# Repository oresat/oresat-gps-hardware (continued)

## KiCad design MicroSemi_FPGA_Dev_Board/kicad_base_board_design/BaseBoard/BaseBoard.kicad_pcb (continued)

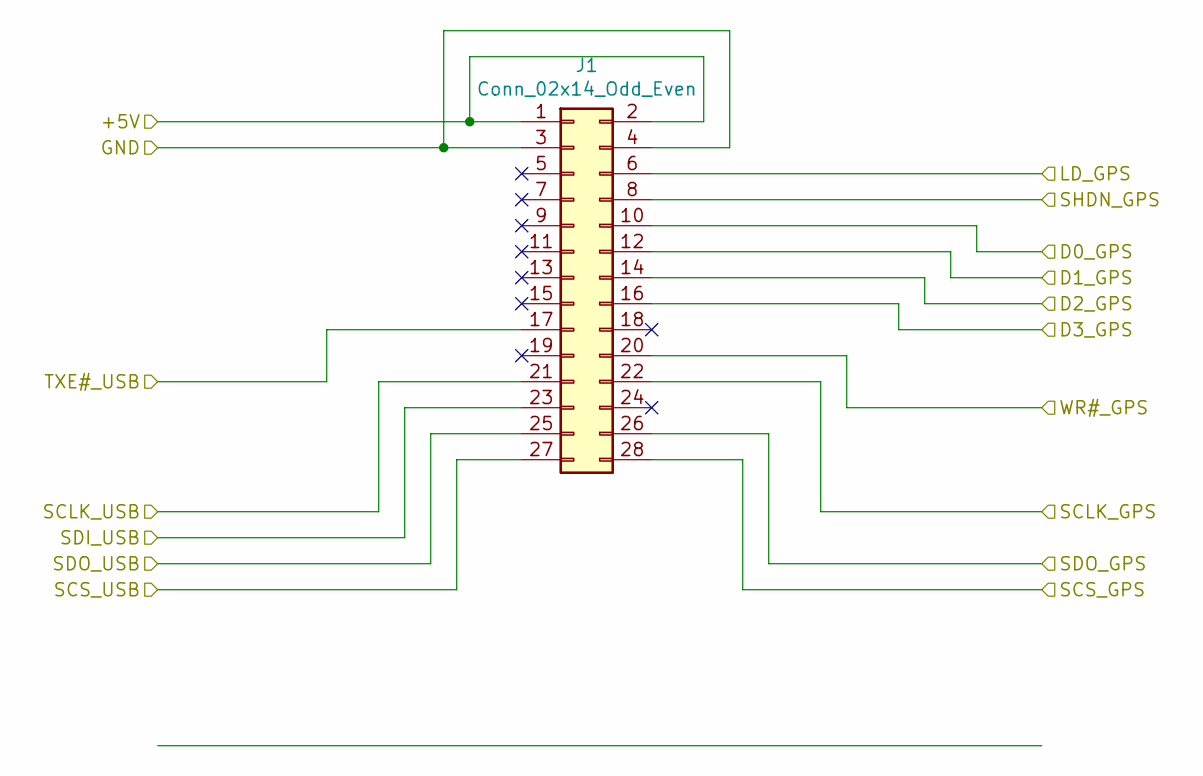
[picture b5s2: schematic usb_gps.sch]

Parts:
J1: Conn_02x14_Odd_Even; PinHeader_2x14_P2.54mm_Vertical

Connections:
/Sheet5DD758E7/+5V: J1.1, J1.2; also elsewhere on the board
/Sheet5DD758E7/D0_GPS: J1.10; also elsewhere on the board
/Sheet5DD758E7/D1_GPS: J1.12; also elsewhere on the board
/Sheet5DD758E7/D2_GPS: J1.14; also elsewhere on the board
/Sheet5DD758E7/D3_GPS: J1.16; also elsewhere on the board
/Sheet5DD758E7/LD_GPS: J1.6; also elsewhere on the board
/Sheet5DD758E7/SCLK_GPS: J1.22; also elsewhere on the board
/Sheet5DD758E7/SCLK_USB: J1.21; also elsewhere on the board
/Sheet5DD758E7/SCS_GPS: J1.28; also elsewhere on the board
/Sheet5DD758E7/SCS_USB: J1.27; also elsewhere on the board
/Sheet5DD758E7/SDI_USB: J1.23; also elsewhere on the board
/Sheet5DD758E7/SDO_GPS: J1.26; also elsewhere on the board
/Sheet5DD758E7/SDO_USB: J1.25; also elsewhere on the board
/Sheet5DD758E7/SHDN_GPS: J1.8; also elsewhere on the board
/Sheet5DD758E7/TXE#_USB: J1.17; also elsewhere on the board
/Sheet5DD758E7/WR#_GPS: J1.20; also elsewhere on the board
GND: J1.3, J1.4; also elsewhere on the board

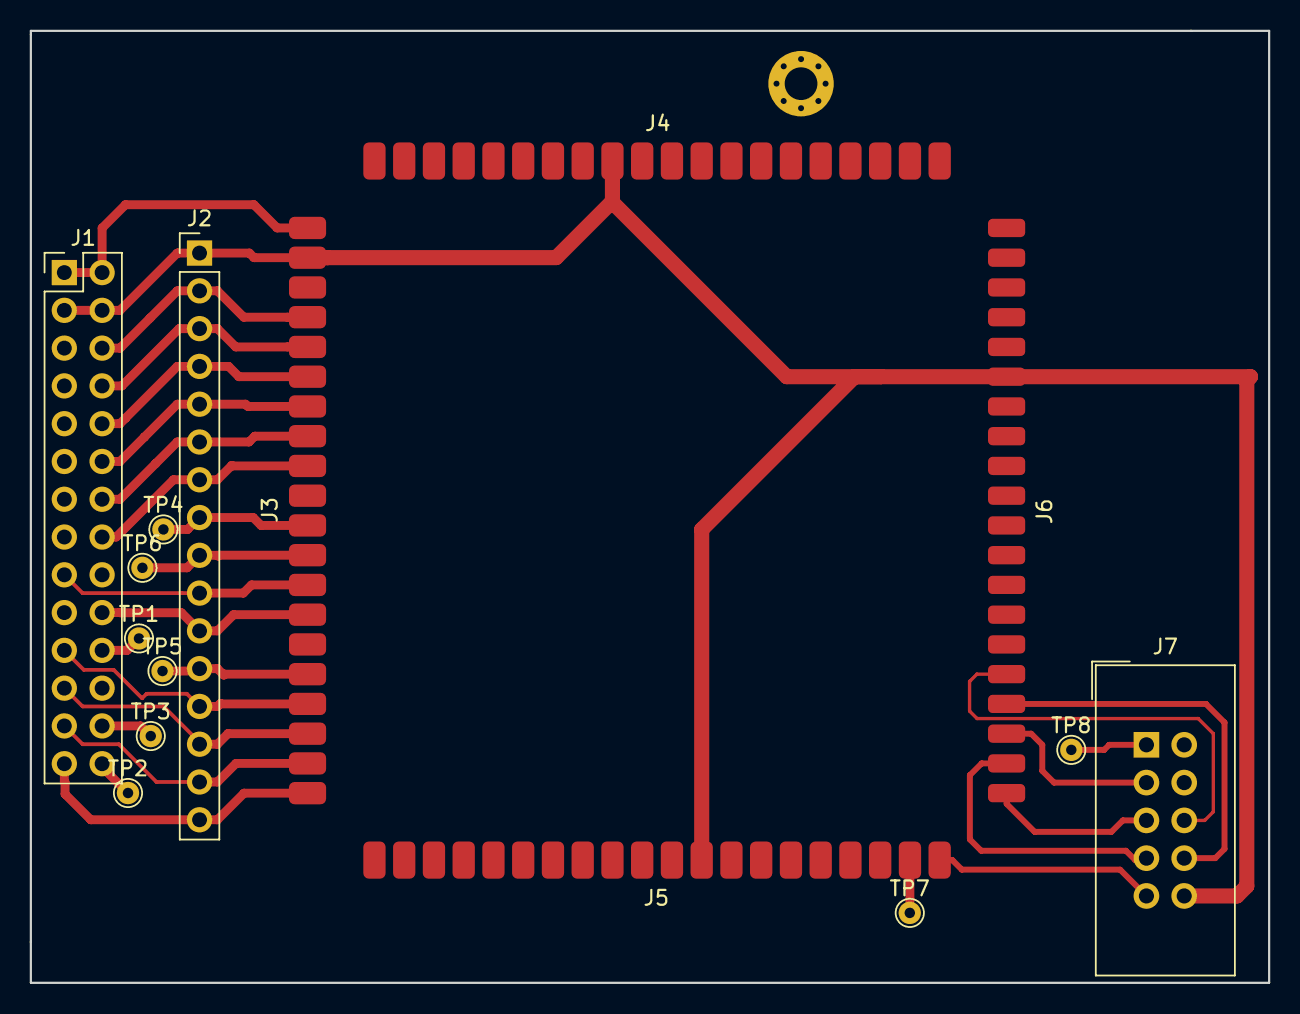
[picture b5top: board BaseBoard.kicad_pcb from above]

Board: 2 copper layers, 83.2 x 64.0 mm, 15 parts (0 on the bottom side), 28 nets.

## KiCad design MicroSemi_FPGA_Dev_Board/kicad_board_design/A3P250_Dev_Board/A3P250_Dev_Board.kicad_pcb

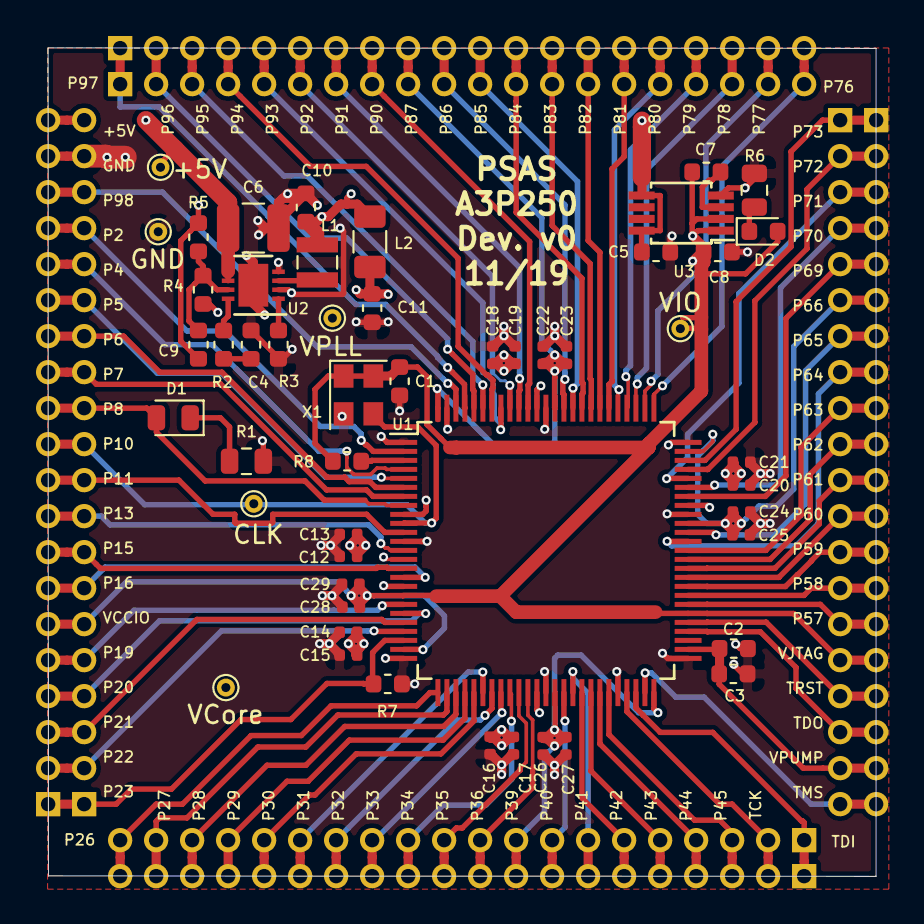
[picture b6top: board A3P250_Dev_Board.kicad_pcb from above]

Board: 4 copper layers, 46.0 x 46.0 mm, 59 parts (0 on the bottom side), 90 nets.

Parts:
+5V: +5V; TestPoint_THTPad_D1.0mm_Drill0.5mm
C1, C3, C7: 0.01uF; C_0603_1608Metric
C2: 0.33uF; C_0603_1608Metric
C4: 680pF; C_0603_1608Metric
C5: 1uF; C_0603_1608Metric
C6: 22uF; C_1210_3225Metric
C8, C10, C11: 10uF; C_0603_1608Metric
C9: 22pF; C_0603_1608Metric
C12, C14, C16, C18, C20, C22, C24, C26, C28: .1uF; C_0402_1005Metric
C13, C15, C17, C19, C21, C23, C25, C27, C29: 0.01uF; C_0402_1005Metric
CLK: VCCIO; TestPoint_THTPad_D1.0mm_Drill0.5mm
D1: LED_ALT; LED_0805_2012Metric
D2: LED_ALT; LED_0603_1608Metric
GND: GND; TestPoint_THTPad_D1.0mm_Drill0.5mm
J1, J1#2, J2, J2#2, J3, J3#2, J4, J4#2: Conn_01x20; PinHeader_1x20_P2.00mm_Vertical
L1: 2.2uH; L_Wuerth_MAPI-2512
L2: 6.8uH; L_1206_3216Metric
R1, R6: 200; R_0805_2012Metric
R2: 16.9K; R_0603_1608Metric
R3: 549K; R_0603_1608Metric
R4: 287K; R_0603_1608Metric
R5: 249K; R_0603_1608Metric
R7, R8: 20K; R_0603_1608Metric
U1: A3P250; LQFP-100_14x14mm_P0.5mm
U2: LTC3561A; DFN-8-1EP_3x3mm_P0.5mm_EP1.66x2.38mm
U3: LT1962-3.3; MSOP-8_3x3mm_P0.65mm
VCore: 1.5V Core; TestPoint_THTPad_D1.0mm_Drill0.5mm
VIO: VCCIO; TestPoint_THTPad_D1.0mm_Drill0.5mm
VPLL: 1.5V PLL; TestPoint_THTPad_D1.0mm_Drill0.5mm
X1: ASE-25MHz; Oscillator_SMD_Abracon_ASE-4Pin_3.2x2.5mm

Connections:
+5V: +5V.1, C5.1, C6.1, J4.20, J4#2.20, U2.5, U2.6, U3.5, U3.8
GAA_IO00RSB0: J4.18, J4#2.18, U1.98
GND: C1.2, C2.2, C3.2, C4.2, C5.2, C6.2, C8.2, C10.2, C11.2, C12.2, C13.2, C14.2, C15.2, C16.2, C17.2, C18.2, C19.2, C20.2, C21.2, C22.2, C23.2, C24.2, C25.2, C26.2, C27.2, C28.2, C29.2, GND.1, J4.19, J4#2.19, R1.2, R3.1, R4.1, R6.2, R7.2, U1.1, U1.9, U1.12, U1.25, U1.38, U1.46, U1.51, U1.67, U1.75, U1.88, U1.99, U2.2, U2.4, U2.9, U3.4, X1.2
unnamed: C4.1, R2.1
unnamed: C7.2, U3.3
unnamed: C9.2, R4.2, R5.2, U2.7
unnamed: C9.1, C10.1, C14.1, C15.1, C16.1, C17.1, C18.1, C19.1, C20.1, C21.1, L1.2, L2.1, R5.1, U1.17, U1.37, U1.68, U1.89, VCore.1
unnamed: C11.1, C12.1, C13.1, L2.2, U1.14, VPLL.1
unnamed: C22.1, C23.1, J1.9, J1#2.9, U1.87, U1.100
unnamed: C24.1, C25.1, J2.6, J2#2.6, U1.66, U1.74
unnamed: C26.1, C27.1, J3.9, J3#2.9, U1.39, U1.50
unnamed: D1.1, R1.1
unnamed: D1.2, J4.12, J4#2.12, U1.8
unnamed: D2.1, R6.1
unnamed: J1.1, J1#2.1, U1.97
unnamed: J1.2, J1#2.2, U1.96
unnamed: J1.3, J1#2.3, U1.95
unnamed: J1.4, J1#2.4, U1.94
unnamed: J1.5, J1#2.5, U1.93
unnamed: J1.6, J1#2.6, U1.92
unnamed: J1.7, J1#2.7, U1.91
unnamed: J1.8, J1#2.8, U1.90
unnamed: J1.10, J1#2.10, U1.86
unnamed: J1.11, J1#2.11, U1.85
unnamed: J1.12, J1#2.12, U1.84
unnamed: J1.13, J1#2.13, U1.83
unnamed: J1.14, J1#2.14, U1.82
unnamed: J1.15, J1#2.15, U1.81
unnamed: J1.16, J1#2.16, U1.80
unnamed: J1.17, J1#2.17, U1.79
unnamed: J1.18, J1#2.18, U1.78
unnamed: J1.19, J1#2.19, U1.77
unnamed: J1.20, J1#2.20, U1.76
unnamed: J2.1, J2#2.1, U1.73
unnamed: J2.2, J2#2.2, U1.72
unnamed: J2.3, J2#2.3, U1.71
unnamed: J2.4, J2#2.4, U1.70
unnamed: J2.5, J2#2.5, U1.69
unnamed: J2.7, J2#2.7, U1.65
unnamed: J2.8, J2#2.8, U1.64
unnamed: J2.9, J2#2.9, U1.63
unnamed: J2.10, J2#2.10, U1.62
unnamed: J2.11, J2#2.11, U1.61
unnamed: J2.12, J2#2.12, U1.60
unnamed: J2.13, J2#2.13, U1.59
unnamed: J2.14, J2#2.14, U1.58
unnamed: J2.15, J2#2.15, U1.57
unnamed: J3.3, J3#2.3, U1.45
unnamed: J3.4, J3#2.4, U1.44
unnamed: J3.5, J3#2.5, U1.43
unnamed: J3.6, J3#2.6, U1.42
unnamed: J3.7, J3#2.7, U1.41
unnamed: J3.8, J3#2.8, U1.40
unnamed: J3.10, J3#2.10, U1.36
unnamed: J3.11, J3#2.11, U1.35
unnamed: J3.12, J3#2.12, U1.34
unnamed: J3.13, J3#2.13, U1.33
unnamed: J3.14, J3#2.14, U1.32
unnamed: J3.15, J3#2.15, U1.31
unnamed: J3.16, J3#2.16, U1.30
unnamed: J3.17, J3#2.17, U1.29
unnamed: J3.18, J3#2.18, U1.28
unnamed: J3.19, J3#2.19, U1.27
unnamed: J3.20, J3#2.20, U1.26
unnamed: J4.1, J4#2.1, R7.1, U1.23
unnamed: J4.2, J4#2.2, U1.22
unnamed: J4.3, J4#2.3, U1.21
unnamed: J4.4, J4#2.4, U1.20
unnamed: J4.5, J4#2.5, U1.19
unnamed: J4.7, J4#2.7, U1.16
unnamed: J4.8, J4#2.8, U1.15
unnamed: J4.9, J4#2.9, U1.13
unnamed: J4.10, J4#2.10, U1.11
unnamed: CLK.1, J4.11, J4#2.11, U1.10, X1.3
unnamed: J4.13, J4#2.13, U1.7
unnamed: J4.14, J4#2.14, U1.6
unnamed: J4.15, J4#2.15, U1.5
unnamed: J4.16, J4#2.16, U1.4
unnamed: J4.17, J4#2.17, U1.2
unnamed: L1.1, U2.3
unnamed: R2.2, U2.8
unnamed: R3.2, U2.1
unnamed: R8.2, U1.3
TCK: J3.2, J3#2.2, U1.47
TDI: J3.1, J3#2.1, U1.48
TDO: J2.18, J2#2.18, U1.54
TMS: J2.20, J2#2.20, U1.49
TRST: J2.17, J2#2.17, U1.55
VCCIB3: C1.1, C7.1, C8.1, C28.1, C29.1, D2.2, J2.16, J2#2.16, J4.6, J4#2.6, R8.1, U1.18, U1.24, U1.56, U3.1, U3.2, VIO.1, X1.1, X1.4
VPUMP: C2.1, C3.1, J2.19, J2#2.19, U1.52

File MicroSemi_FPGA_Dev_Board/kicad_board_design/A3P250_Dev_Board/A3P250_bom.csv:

Refs,Value,Footprint,Quantity,MFR,MPN,SPR,SPN
C12;C14;C16;C20;C18,.1uF,Capacitor_SMD:C_0402_1005Metric,5,-,CGA2B1X7R1C104K050BC,Digikey,445-5613-1-ND
C13;C17;C21;C19;C15;C3;C7;C1,0.01uF,Capacitor_SMD:C_0603_1608Metric,8,Kemet,C0603C103K5RAC7081,Digikey,399-C0603C103K5RAC7081CT-ND
C2,0.33uF,Capacitor_SMD:C_0603_1608Metric,1,Yageo,CC0603KRX5R7BB334,Digikey,311-4045-1-ND
C10;C8;C11,10uF,Capacitor_SMD:C_0603_1608Metric,3,Taiyo Yuden,JMK107BJ106MA-T,Digikey,587-1256-1-ND
C5,1uF,Capacitor_SMD:C_0603_1608Metric,1,Samsung,CL10B105KP8NNNC,Digikey,1276-1946-1-ND
C9,22pF,Capacitor_SMD:C_0603_1608Metric,1,Yageo,CC0603JRNPO9BN220,Digikey,311-1062-1-ND
C4,680pF,Capacitor_SMD:C_0603_1608Metric,1,Yageo,CC0603KRX7R9BB681,Digikey,311-1188-1-ND
C6,22uF,Capacitor_SMD:C_1210_3225Metric,1,Taiyo Yuden,JMK325BJ226MM-T,Digikey,587-1384-1-ND
J1;J4;J2;J3,Conn_01x20,Connector_PinHeader_2.00mm:PinHeader_1x20_P2.00mm_Vertical,4,-,-,-,-
L2,6.8uH,Inductor_SMD:L_1206_3216Metric,1,Taiyo Yuden,CB2518T6R8M,Digikey,587-2188-1-ND
L1,2.2uH,Inductor_SMD:L_Wuerth_MAPI-2512,1,Wurth,74405024022,Digikey,732-10776-1-ND
D2,LED_ALT,LED_SMD:LED_0603_1608Metric,1,Lite-On,LTST-C191KGKT,Digikey,160-1446-2-ND
D1,LED_ALT,LED_SMD:LED_0805_2012Metric,1,Lite-On,LTST-C171KRKT,Digikey,160-1427-1-ND
X1,ASE-25MHz,Oscillator:Oscillator_SMD_Abracon_ASE-4Pin_3.2x2.5mm,1,Abracon,ASE-25.000MHZ-LC-T,Digikey,535-9568-1-ND
U2,LTC3561A,Package_DFN_QFN:DFN-8-1EP_3x3mm_P0.5mm_EP1.66x2.38mm,1,Analog Devices,LTC3561AEDD#TRPBFCT-ND,Digikey,LTC3561AEDD#TRPBFCT-ND
U1,A3P250,Package_QFP:LQFP-100_14x14mm_P0.5mm,1,Microsemi,A3P250-VQG100,Digikey,1100-1030-ND
U3,LT1962-3.3,Package_SO:MSOP-8_3x3mm_P0.65mm,1,Analog Devices,LT1962EMS8-3.3#PBF,Digikey,LT1962EMS8-3.3#PBF-ND
R2,16.9K,Resistor_SMD:R_0603_1608Metric,1,Yageo,RT0603DRE0716K9L,Digikey,311-2441-1-ND
R5,249K,Resistor_SMD:R_0603_1608Metric,1,Yageo,RT0603BRD07249KL,Digikey,YAG4510CT-ND
R4,287K,Resistor_SMD:R_0603_1608Metric,1,Yageo,RT0603BRD07287KL,Digikey,YAG1609CT-ND
R3,549K,Resistor_SMD:R_0603_1608Metric,1,Yageo,RC0603FR-07549KL,Digikey,311-549KHRCT-ND
R6;R1,200,Resistor_SMD:R_0805_2012Metric,2,Susumu,RR1220P-201-D,Digikey,RR12P200DCT-ND

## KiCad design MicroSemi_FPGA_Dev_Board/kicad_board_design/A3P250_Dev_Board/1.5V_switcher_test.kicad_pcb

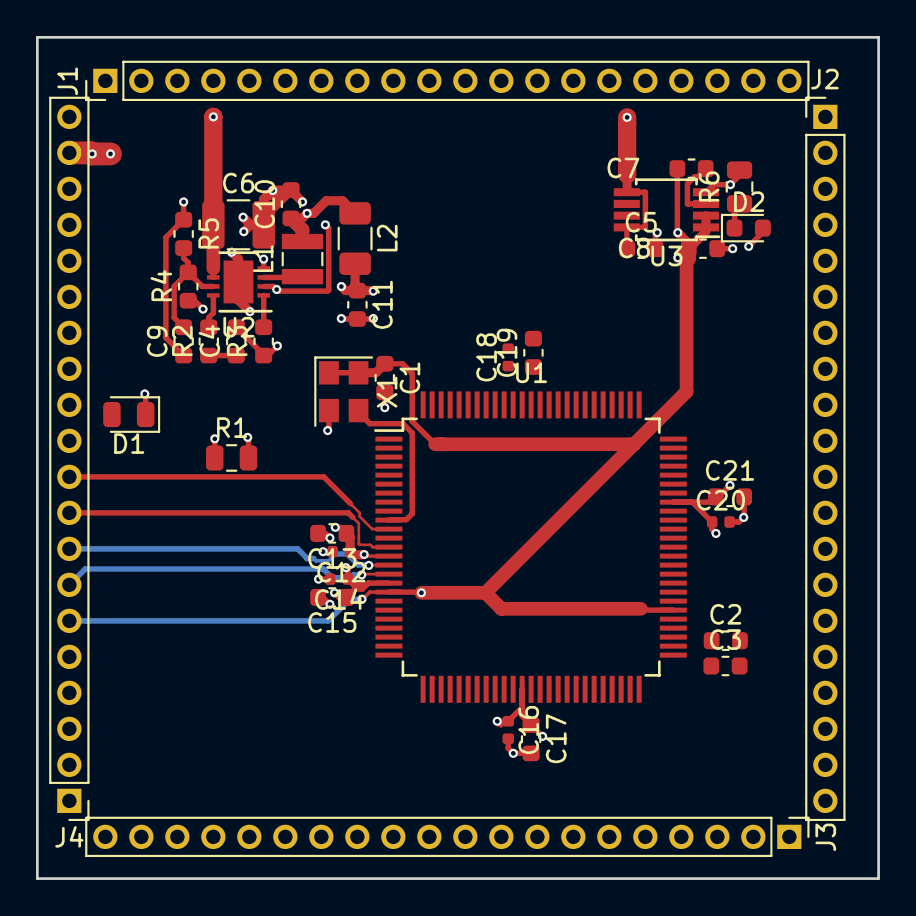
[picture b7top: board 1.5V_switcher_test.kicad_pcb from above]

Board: 4 copper layers, 46.7 x 46.7 mm, 39 parts (0 on the bottom side), 89 nets.

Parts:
C1, C3, C7, C13, C15, C17, C19, C21: 0.01uF; C_0603_1608Metric
C2: 0.33uF; C_0603_1608Metric
C4: 680pF; C_0603_1608Metric
C5: 1uF; C_0603_1608Metric
C6: 22uF; C_1210_3225Metric
C8, C10, C11: 10uF; C_0603_1608Metric
C9: 22pF; C_0603_1608Metric
C12, C14, C16, C18, C20: .1uF; C_0402_1005Metric
D1: LED_ALT; LED_0805_2012Metric
D2: LED_ALT; LED_0603_1608Metric
J1, J2, J3, J4: Conn_01x20; PinHeader_1x20_P2.00mm_Vertical
L1: 2.2uH; L_Wuerth_MAPI-2512
L2: 6.8uH; L_1206_3216Metric
R1, R6: 200; R_0805_2012Metric
R2: 16.9K; R_0603_1608Metric
R3: 549K; R_0603_1608Metric
R4: 287K; R_0603_1608Metric
R5: 249K; R_0603_1608Metric
U1: A3P250; LQFP-100_14x14mm_P0.5mm
U2: LTC3561A; DFN-8-1EP_3x3mm_P0.5mm_EP1.66x2.38mm
U3: LT1962-3.3; MSOP-8_3x3mm_P0.65mm
X1: ASE-25MHz; Oscillator_SMD_Abracon_ASE-4Pin_3.2x2.5mm

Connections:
+5V: C5.1, C6.1, J4.20, U2.5, U2.6, U3.5, U3.8
GAA_IO00RSB0: J4.17, U1.98
GND: C1.2, C2.2, C3.2, C4.2, C5.2, C6.2, C8.2, C10.2, C11.2, C12.2, C13.2, C14.2, C15.2, C16.2, C17.2, C18.2, C19.2, C20.2, C21.2, J4.19, R1.2, R3.1, R4.1, R6.2, U1.1, U1.9, U1.12, U1.24, U1.25, U1.38, U1.46, U1.50, U1.51, U1.67, U1.74, U1.75, U1.88, U1.99, U1.100, U2.2, U2.4, U2.9, U3.4, X1.2
unnamed: C4.1, R2.1
unnamed: C7.2, U3.3
unnamed: C9.2, R4.2, R5.2, U2.7
unnamed: C9.1, C10.1, C14.1, C15.1, C16.1, C17.1, C18.1, C19.1, C20.1, C21.1, L1.2, L2.1, R5.1, U1.17, U1.37, U1.68, U1.89
unnamed: C11.1, C12.1, C13.1, L2.2, U1.14
unnamed: D1.1, R1.1
unnamed: D1.2, J4.12, U1.8
unnamed: D2.1, R6.1
unnamed: J1.1, U1.97
unnamed: J1.2, U1.96
unnamed: J1.3, U1.95
unnamed: J1.4, U1.94
unnamed: J1.5, U1.93
unnamed: J1.6, U1.92
unnamed: J1.7, U1.91
unnamed: J1.8, U1.90
unnamed: J1.9, U1.87
unnamed: J1.10, U1.86
unnamed: J1.11, U1.85
unnamed: J1.12, U1.84
unnamed: J1.13, U1.83
unnamed: J1.14, U1.82
unnamed: J1.15, U1.81
unnamed: J1.16, U1.80
unnamed: J1.17, U1.79
unnamed: J1.18, U1.78
unnamed: J1.19, U1.77
unnamed: J1.20, U1.76
unnamed: J2.1, U1.73
unnamed: J2.2, U1.72
unnamed: J2.3, U1.71
unnamed: J2.4, U1.70
unnamed: J2.5, U1.69
unnamed: J2.6, U1.66
unnamed: J2.7, U1.65
unnamed: J2.8, U1.64
unnamed: J2.9, U1.63
unnamed: J2.10, U1.62
unnamed: J2.11, U1.61
unnamed: J2.12, U1.60
unnamed: J2.13, U1.59
unnamed: J2.14, U1.58
unnamed: J2.15, U1.57
unnamed: J3.3, U1.45
unnamed: J3.4, U1.44
unnamed: J3.5, U1.43
unnamed: J3.6, U1.42
unnamed: J3.7, U1.41
unnamed: J3.8, U1.40
unnamed: J3.9, U1.39
unnamed: J3.10, U1.36
unnamed: J3.11, U1.35
unnamed: J3.12, U1.34
unnamed: J3.13, U1.33
unnamed: J3.14, U1.32
unnamed: J3.15, U1.31
unnamed: J3.16, U1.30
unnamed: J3.17, U1.29
unnamed: J3.18, U1.28
unnamed: J3.19, U1.27
unnamed: J3.20, U1.26
unnamed: J4.1, U1.23
unnamed: J4.2, U1.22
unnamed: J4.3, U1.21
unnamed: J4.4, U1.20
unnamed: J4.5, U1.19
unnamed: J4.7, U1.16
unnamed: J4.8, U1.15
unnamed: J4.9, U1.13
unnamed: J4.10, U1.11
unnamed: J4.11, U1.10, X1.3
unnamed: J4.13, U1.7
unnamed: J4.14, U1.6
unnamed: J4.15, U1.5
unnamed: J4.16, U1.4
unnamed: J4.18, U1.2
unnamed: L1.1, U2.3
unnamed: R2.2, U2.8
unnamed: R3.2, U2.1
TCK: J3.2, U1.47
TDI: J3.1, U1.48
TDO: J2.18, U1.54
TMS: J2.20, U1.49
TRST: J2.17, U1.55
VCCIB3: C1.1, C7.1, C8.1, D2.2, J2.16, J4.6, U1.18, U1.56, U3.1, U3.2, X1.1, X1.4
VPUMP: C2.1, C3.1, J2.19, U1.52

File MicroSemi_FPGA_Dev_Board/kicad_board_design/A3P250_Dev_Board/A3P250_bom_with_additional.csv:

Refs,Value,Footprint,Quantity,MFR,MPN,SPR,SPN
C12;C14;C16;C20;C18,.1uF,Capacitor_SMD:C_0402_1005Metric,5(9),-,CGA2B1X7R1C104K050BC,Digikey,445-5613-1-ND
C13;C17;C21;C19;C15;C3;C7;C1,0.01uF,Capacitor_SMD:C_0603_1608Metric,8(12),Kemet,C0603C103K5RAC7081,Digikey,399-C0603C103K5RAC7081CT-ND
C2,0.33uF,Capacitor_SMD:C_0603_1608Metric,1,Yageo,CC0603KRX5R7BB334,Digikey,311-4045-1-ND
C10;C8;C11,10uF,Capacitor_SMD:C_0603_1608Metric,3,Taiyo Yuden,JMK107BJ106MA-T,Digikey,587-1256-1-ND
C5,1uF,Capacitor_SMD:C_0603_1608Metric,1,Samsung,CL10B105KP8NNNC,Digikey,1276-1946-1-ND
C9,22pF,Capacitor_SMD:C_0603_1608Metric,1,Yageo,CC0603JRNPO9BN220,Digikey,311-1062-1-ND
C4,680pF,Capacitor_SMD:C_0603_1608Metric,1,Yageo,CC0603KRX7R9BB681,Digikey,311-1188-1-ND
C6,22uF,Capacitor_SMD:C_1210_3225Metric,1,Taiyo Yuden,JMK325BJ226MM-T,Digikey,587-1384-1-ND
J1;J4;J2;J3,Conn_01x20,Connector_PinHeader_2.00mm:PinHeader_1x20_P2.00mm_Vertical,4,-,-,-,-
L2,6.8uH,Inductor_SMD:L_1206_3216Metric,1,Taiyo Yuden,CB2518T6R8M,Digikey,587-2188-1-ND
L1,2.2uH,Inductor_SMD:L_Wuerth_MAPI-2512,1,Wurth,74405024022,Digikey,732-10776-1-ND
D2,LED_ALT,LED_SMD:LED_0603_1608Metric,1,Lite-On,LTST-C191KGKT,Digikey,160-1446-2-ND
D1,LED_ALT,LED_SMD:LED_0805_2012Metric,1,Lite-On,LTST-C171KRKT,Digikey,160-1427-1-ND
X1,ASE-25MHz,Oscillator:Oscillator_SMD_Abracon_ASE-4Pin_3.2x2.5mm,1,Abracon,ASE-25.000MHZ-LC-T,Digikey,535-9568-1-ND
U2,LTC3561A,Package_DFN_QFN:DFN-8-1EP_3x3mm_P0.5mm_EP1.66x2.38mm,1,Analog Devices,LTC3561AEDD#TRPBFCT-ND,Digikey,LTC3561AEDD#TRPBFCT-ND
U1,A3P250,Package_QFP:LQFP-100_14x14mm_P0.5mm,1,Microsemi,A3P250-VQG100,Digikey,1100-1030-ND
U3,LT1962-3.3,Package_SO:MSOP-8_3x3mm_P0.65mm,1,Analog Devices,LT1962EMS8-3.3#PBF,Digikey,LT1962EMS8-3.3#PBF-ND
R2,16.9K,Resistor_SMD:R_0603_1608Metric,1,Yageo,RT0603DRE0716K9L,Digikey,311-2441-1-ND
R5,249K,Resistor_SMD:R_0603_1608Metric,1,Yageo,RT0603BRD07249KL,Digikey,YAG4510CT-ND
R4,287K,Resistor_SMD:R_0603_1608Metric,1,Yageo,RT0603BRD07287KL,Digikey,YAG1609CT-ND
R3,549K,Resistor_SMD:R_0603_1608Metric,1,Yageo,RC0603FR-07549KL,Digikey,311-549KHRCT-ND
R6;R1,200,Resistor_SMD:R_0805_2012Metric,2,Susumu,RR1220P-201-D,Digikey,RR12P200DCT-ND
,,,,,,,
,,,,,,,
,,,,,,,
,,FlashPro5,,,,,1100-1179-ND
,,JTAG header,,,,,A26267-ND
,,breakaway header (38 pins),,,,,S1012EC-38-ND

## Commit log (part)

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2019-03-20 Moving the GPS USB front end board from PSAS repo.
2019-07-18 Fix 3.3V LDO inhibit polarity.
2019-07-18 Fix footprint for MAX 8510 (two places).
2019-07-20 Change out micro-usb connector to one with thru holes.
2019-07-20 Change out SMA connector for thru-hole version.
2019-07-22 Add back mounting holes, rev. front silk.
2019-07-24 Minor cleanup.
2019-07-26 Update to MAX2771. Changes to decoupling caps, Remove ANTFLAG, IDLE signals. Add explicit antenna bias. New matching network for LNA input. Remove bypass for SAW filter.
2019-07-27 Add some footprints, annotate new parts, generate netlist, EDR check.
2019-07-27 Intermediate routing.
2019-07-28 Changed 2.2uF to 10uF. Completed routing. Added via fencing and footprint vias.
2019-07-28 Final cleanup before submit to OSHPARK.
2019-08-02 Fix value display on EEPROM. Consolidate some part values.
2019-08-20 "auto-generated from update_repos.py"
2019-09-15 as sent to OSHPARK
2019-10-30 Add more decoupling caps to 2232H.
2019-10-30 Run DRC, generate and import netlist w/ new caps.
2019-11-01 Partially laid out; ready to move some parts.
2019-11-01 Moved optional Maxim clk fix circuit to FTDI side.
2019-11-01 Now passes DRC.
2019-11-01 Plotted gerbers. Fixed crystal load caps, added LED, added stitching.
2019-11-02 Change SMA footprint, add SAW filter, extend header pins.
2019-11-03 Add signals to header.
2019-11-13 Add LED P/N. Process BOM prior to order.
2019-11-17 Add in Microsemi A3P250 development board. Layout almost completed.
2019-11-17 Routed, fixed labels, added test points.
2019-12-01 Add solder paste layer.
2020-09-27 Added cobbled together star tracker + rocket SDR GPS receiver
2021-01-24 GPS card has been mostly layed out. Still missing a few things, but nothing major.
2021-01-24 Added some polygons to the power plane
2021-02-01 Finished laying out Venus receiver. Fixed issue with GND and AGND planes. Added vias, and restrict lines to separate digital and RF ground planes. Added enable lines to Max and Venus receivers. Updat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
2021-02-01 Fixed a note in the schematic
2021-02-03 Updated boot circuitry. Cleaned up names layer.
2021-02-06 Moved some silk screen items out of the way of pads
2021-02-08 Fixed design review things: made net names more clear, removed solder mask from top of RF traces, opened up space around octavo 3.3v pads, moved digital LDO for the max chip, added pin header and thr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
2021-02-20 Fixed 3.3VA rail for I2C protection chip.
2021-02-28 Added attributes to some parts, and changed internal cutout polygons to 0.1 width instead of 0 width.
2021-03-01 Updated oscillator capacitor values and added BOM
2021-03-08 OK'd ERC errors.
2021-03-25 Updated BOM after stuffing v1.0: added shield, a 1uF was accidentally marked as 0.1 uF, and since the supercap is DNP, stuff the diode and resistor associated with 0 ohm 0603 resistors.
2022-08-02 Updated gitignore for kicad files
2022-08-02 Moved old EAGLE files to separate folder
2022-10-02 GPS card is in KiCad now
2022-10-02 Added separation between digital and RF gnd
2023-01-22 GPS card design review changes and issue fixes
2023-01-22 Changed GPS card schematic sheet naming convention
2023-01-22 Updated schematic sheet links to match new naming
2023-01-22 Fixed date on GPS card
2023-01-22 Quick GPS card design review changes
2023-07-20 Updated GPS card with changes from C3 and notes. Fixed library issues
2023-08-31 Updated GPS card
2024-01-02 Update RF path for sunstone board run, and connected VPD diodes
2024-01-02 Updated library paths for GPS card schematic
2024-01-02 Cleaned up ERC and DRC errors on GPS card
2024-01-02 Version 1.1 of the GPS card, now in KiCAD. Updated .gitignore file, too.
2024-01-18 Added license file. Also small changd to DRU and power planes.
2024-01-18 3D model of eMMC
2024-05-25 Updated KiCAD 8, updated schematic sheet info, polished some schematic things, and made DNP parts DNP.
2026-06-22 updated symbols and started new 2771 symbol
2026-06-23 Routine push
    Began update to GPS chip
2026-06-24 Routine push
    Reference schematic pasted for MAX2769
2026-06-24 Routine Push
    Andrew should look at the MAX2769 change.
2026-06-25 Routine Push
    Various small changes made
2026-06-26 Routine Push
    First attempt to clean up schematic
2026-06-27 Routine Push
    Schematic finished. Components laid out, chasing ERCs.
2026-06-28 Routine Push
2026-06-29 Push for Layout review
2026-06-29 Cleaned up silkscreen
2026-06-29 General cleanup of schematic and layout
    Updated .gitignore, updates DRU file, moved RF lines to RF-50-MIN (max is just too big),
    lots of cleanup on the root page to make it pretty, cleaned up some redudant labels,
    updated SMPM connector and added rule zone, updated PCB outline to include NPTH drills
    for SMPM connectors, began cleanup of OPD.
2026-06-29 Set up makefile for build
2026-06-30 Minor layout changes
